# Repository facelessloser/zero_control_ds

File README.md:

# zero_control_ds
zero_control_ds

Blog post - https://facelesstech.wordpress.com/2019/07/06/zero-control-ds-edition/
Youtube - https://youtu.be/p-8UkPMX_BI

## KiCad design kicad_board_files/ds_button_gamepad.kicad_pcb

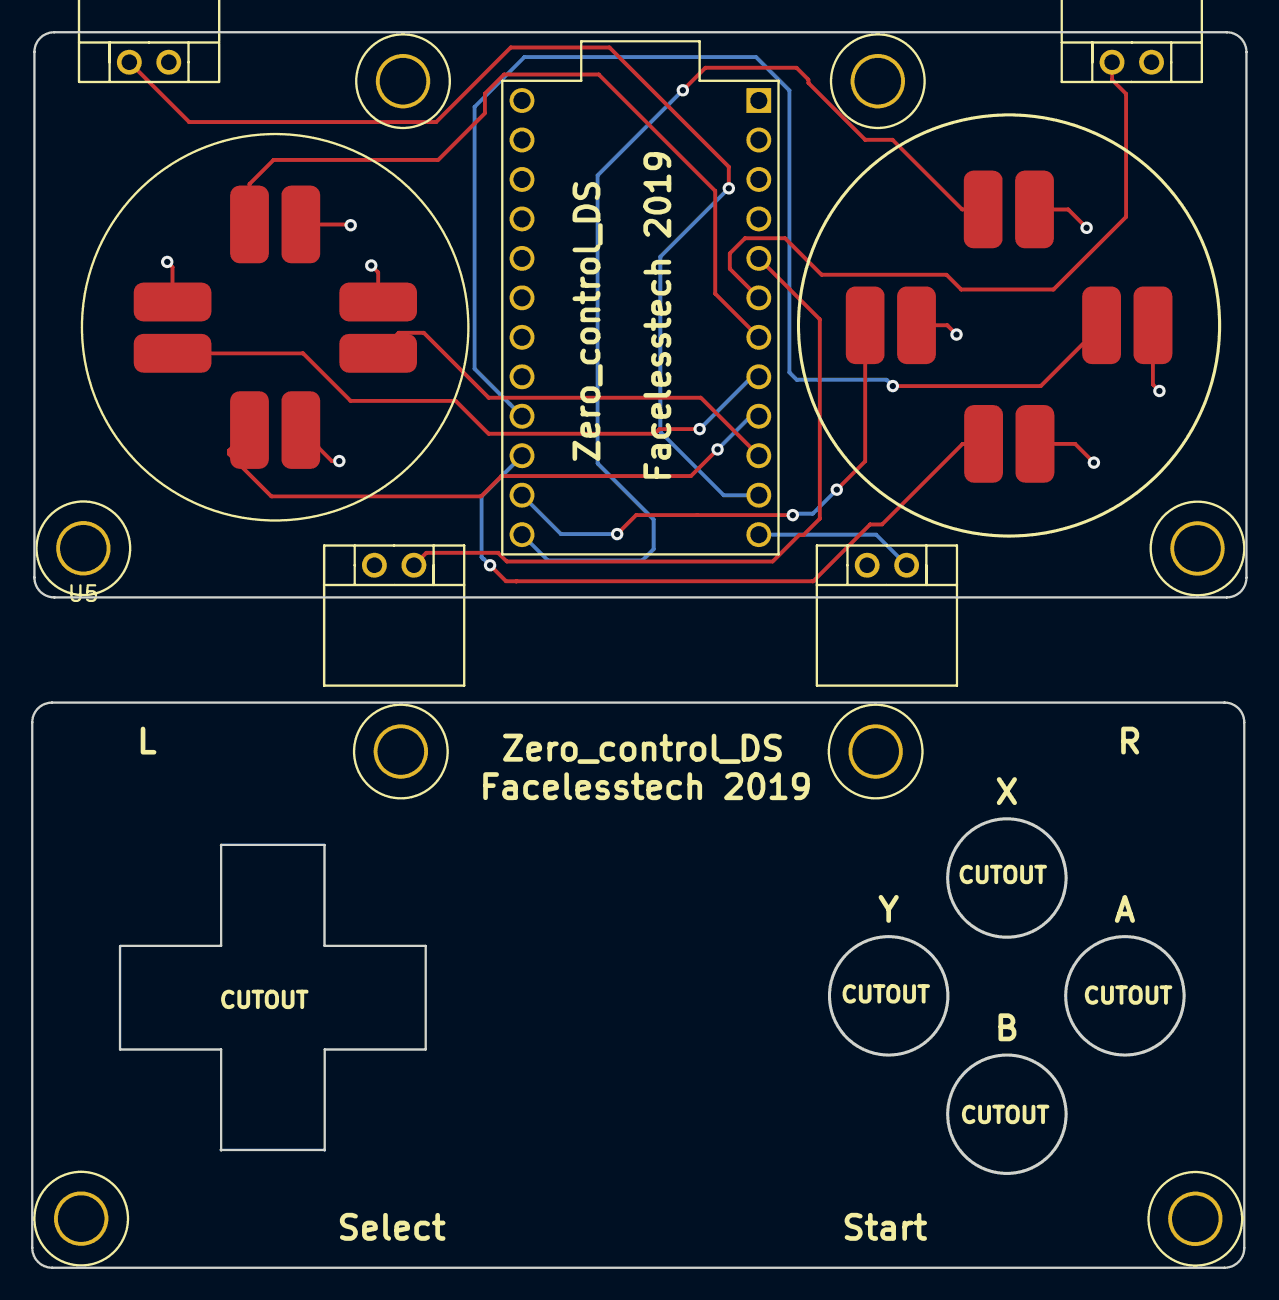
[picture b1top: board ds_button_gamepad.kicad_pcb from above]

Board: 2 copper layers, 78.1 x 79.5 mm, 21 parts (1 on the bottom side), 13 nets.

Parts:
SW1, SW2, SW3, SW4, SW5, SW6, SW7, SW8: SW_Push; gbc_buttons_custom
SW9, SW10, SW11, SW12: SW_Push; right_angle_2_pin
U1: ProMicro
U2, U2#2, U3, U3#2, U4, U4#2, U5, U5#2: m3_standsoffs; m3_hole_custom

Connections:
unnamed: SW1.1, U1.8
unnamed: SW1.2, SW2.2, SW3.2, SW4.2, SW5.2, SW6.2, SW7.2, SW8.2, SW9.2, SW10.2, SW11.2, SW12.2, U1.23
unnamed: SW2.1, U1.10
unnamed: SW3.1, U1.7
unnamed: SW4.1, U1.9
unnamed: SW5.1, U1.13
unnamed: SW6.1, U1.15
unnamed: SW7.1, U1.14
unnamed: SW8.1, U1.16
unnamed: SW9.1, U1.5
unnamed: SW10.1, U1.11
unnamed: SW11.1, U1.12
unnamed: SW12.1, U1.6

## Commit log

2019-06-30 Board files
2019-06-30 arduino sketch
2019-07-06 board files for right angled buttons
2020-02-27 added links to readme
